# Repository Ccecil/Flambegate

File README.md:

# Flambegate
Failsafe Highside shutoff FET for 3d printers 

Flambegate is an attempt at adding hardware failsafes to 3d printers to add a layer of protection above and beyond what the standard hardware does.  This adds a "highside fet control" to the hotend so that it can be shutdown in case of fault.
Can be controlled by "dumb" devices such as my ThermistorComparator board.

-Standalone option via optional 5v Recom regulator
-Safely switches up to ~8a @28v DC
-Inline fuseholder added
-Can use Amass XT30 Horizontal or vertical connectors or bare wires (strain relief holes in board)

Available at: https://www.robosprout.com/product/flambegate-v0-1/

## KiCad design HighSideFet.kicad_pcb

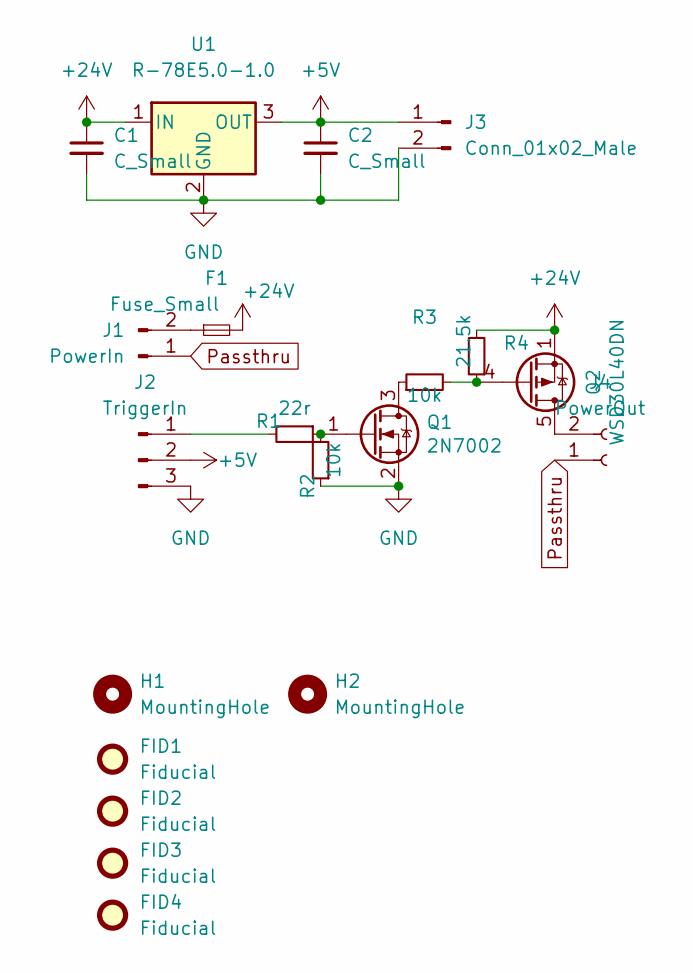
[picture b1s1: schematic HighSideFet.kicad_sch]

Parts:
C1, C2: C_Small; C_1206_3216Metric
F1: Fuse_Small; Fuseholder_Blade_Mini_Keystone_3568
FID1, FID2, FID3, FID4: Fiducial; Fiducial_0.75mm_Mask1.5mm
H1, H2: MountingHole; MountingHole_2.5mm
J1: PowerIn; AMASS_XT30PW-M_1x02_P2.50mm_Horizontal
J2: TriggerIn; Molex_KK-254_AE-6410-03A_1x03_P2.54mm_Vertical
J3: Conn_01x02_Male; Molex_KK-254_AE-6410-02A_1x02_P2.54mm_Vertical
J4: PowerOut; AMASS_XT30PW-F_1x02_P2.50mm_Horizontal
Q1: 2N7002; SOT-23
Q2: WSD30L40DN; Vishay_PowerPAK_1212-8_Single
R1: 22r; R_0402_1005Metric
R2, R3: 10k; R_0402_1005Metric
R4: 21.5k; R_0402_1005Metric
U1: R-78E5.0-1.0; Converter_DCDC_RECOM_R-78E-0.5_THT

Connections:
+5V: C2.1, J2.2, J3.1, U1.3 (OUT)
+24V: C1.1, F1.2, Q2.1 (S), Q2.2 (S), Q2.3 (S), R4.2, U1.1 (IN)
GND: C1.2, C2.2, J2.3, J3.2, Q1.2 (S), R2.1, U1.2 (GND)
unnamed: F1.1, J1.2
unnamed: J2.1, R1.2
unnamed: Q1.1 (G), R1.1, R2.2
unnamed: Q1.3 (D), R3.1
unnamed: Q2.4 (G), R3.2, R4.1
unnamed: J4.2, Q2.5 (D)
Passthru: J1.1, J4.1

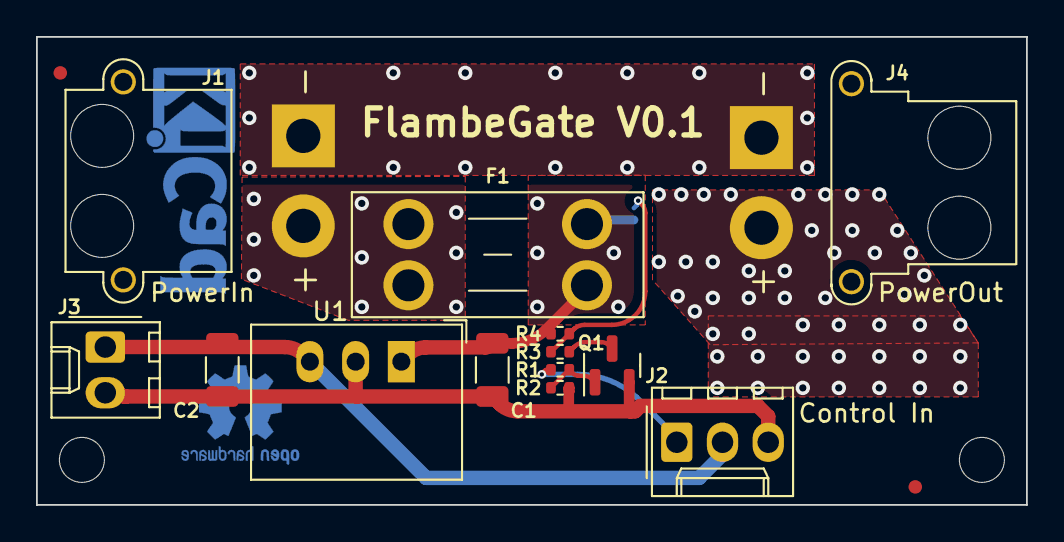
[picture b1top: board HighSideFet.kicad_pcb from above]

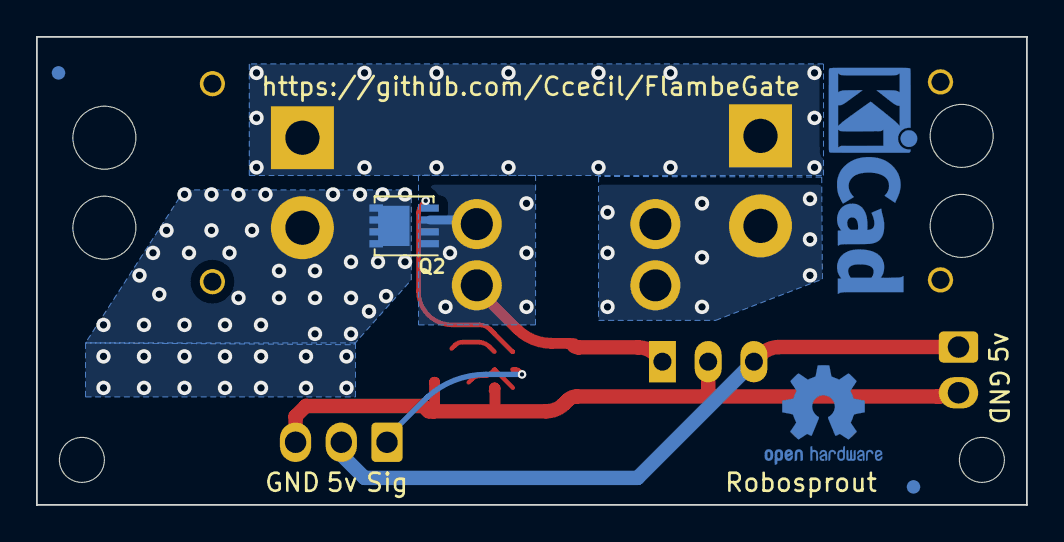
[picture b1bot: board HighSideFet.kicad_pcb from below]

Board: 2 copper layers, 55.0 x 26.0 mm, 20 parts (3 on the bottom side), 10 nets.
